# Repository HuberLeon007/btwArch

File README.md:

**Autor:** Leon Huber [leonerwinhube@gmail.com](mailto:leonerwinhube@gmail.com)  
**Datum:** 2025-04-29  

---
# btwArch

btwArch is a custom mechanical macropad designed because I use Arch btw. This hackpad features a sleek design with customizable keys, RGB lighting, and modern connectivity options to enhance your workflow.

Built as part of the HackClub 2025 initiative, this project serves as both a functional tool and a learning experience in PCB design, 3D modeling, and firmware development.    
(It was my first HackClub <3)

## Overall Design:
Here's the complete assembled btwArch showing the final product in action:

*The finished btwArch ready for daily use*

## CAD Model & Case Design:
The case features a modern, minimalist design with precise tolerances for perfect component fit. The assembly uses standard hardware for easy manufacturing and repair.

*3D model showing how all components fit together from different angles*

## PCB Design
The PCB was designed with modern best practices, featuring proper ground planes, optimized routing, and robust component placement.

**Schematic:**

*Complete electrical schematic showing all connections*

**PCB Layout:**

*Final PCB layout with optimized routing and component placement*

## Firmware Overview
btwArch runs on KMK firmware, a powerful and flexible keyboard firmware that allows for extensive customization and macro programming.

**Features:**
- Customizable key macros via KMK
- RGB lighting effects and patterns

## Bill of Materials (BOM):

| Component | Quantity | Specification |
|-----------|----------|---------------|
| Mechanical Switches | 3x | Cherry MX Switches |
| Keycaps | 3x | Blank DSA keycaps (White) |
| RGB LEDs | 8x | SK6812 MINI-E LEDs |
| Microcontroller | 1x | Seeed XIAO RP2040-SMD |
| Resistors | 1 | 63 ohm |
| Case | 1 | 2 printed parts |

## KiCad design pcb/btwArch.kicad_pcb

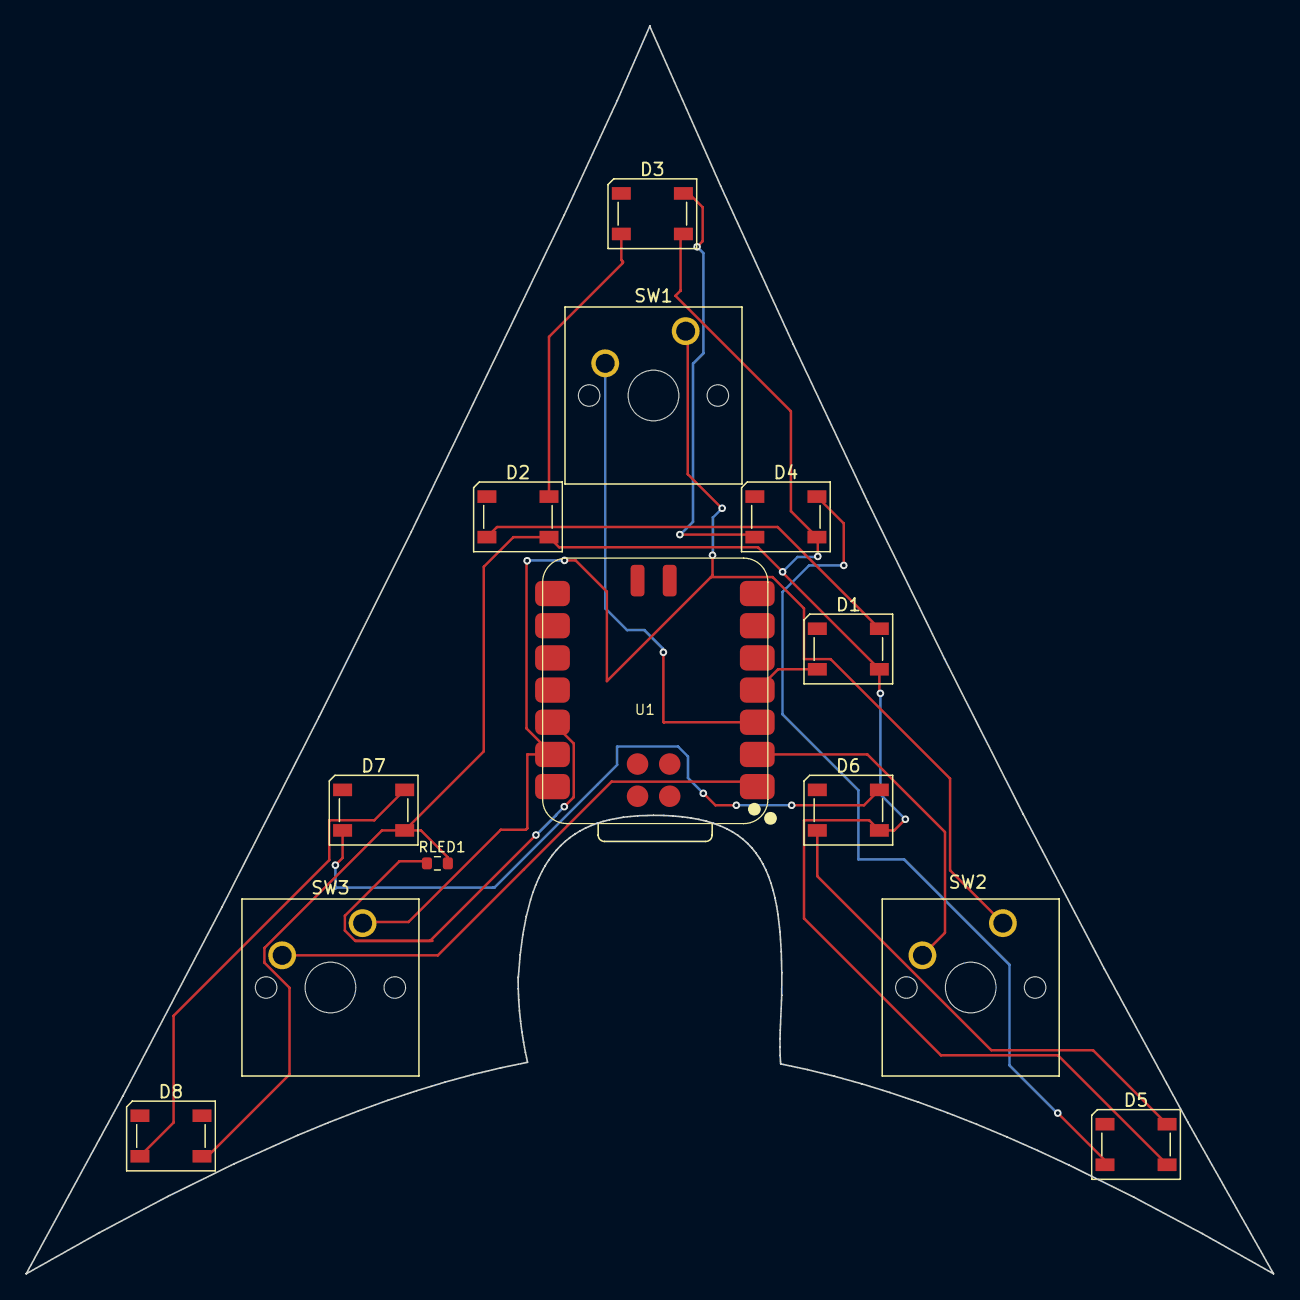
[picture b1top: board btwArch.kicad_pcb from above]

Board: 2 copper layers, 98.5 x 98.5 mm, 13 parts (0 on the bottom side), 14 nets.

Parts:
D1, D2, D3, D4, D5, D6, D7, D8: SK6812; LED_SK6812_PLCC4_5.0x5.0mm_P3.2mm
RLED1: 62; R_0603_1608Metric
SW1, SW2, SW3: SW_Push; SW_Cherry_MX_1.00u_PCB
U1: XIAO-RP2040-SMD

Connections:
GND: SW1.1, SW2.1, SW3.1, U1.13 (GND)
unnamed: D1.2 (DIN), U1.4 (GPIO29_A3_D3)
unnamed: D1.4 (DOUT), D2.2 (DIN)
unnamed: D1.3 (VDD), D2.3 (VDD), D3.3 (VDD), D4.3 (VDD), D5.3 (VDD), D6.3 (VDD), D7.3 (VDD), D8.3 (VDD), RLED1.2
unnamed: D2.4 (DOUT), D3.2 (DIN)
unnamed: D3.4 (DOUT), D4.2 (DIN)
unnamed: D4.4 (DOUT), D5.2 (DIN)
unnamed: D5.4 (DOUT), D6.2 (DIN)
unnamed: D6.4 (DOUT), D7.2 (DIN)
unnamed: D7.4 (DOUT), D8.2 (DIN)
unnamed: RLED1.1, U1.12 (3V3)
unnamed: SW3.2, U1.1 (GPIO26_A0_D0)
unnamed: SW2.2, U1.2 (GPIO27_A1_D1)
unnamed: SW1.2, U1.3 (GPIO28_A2_D2)

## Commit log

2025-06-25 done
2025-06-26 Update README and PCB schematic: add banner image and modify power symbol placement
2025-06-26 demo
